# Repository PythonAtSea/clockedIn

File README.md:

# ClockedIn

> stupid name i know

insert readme stuffsies

## BOM
| Name | Link | Price |
|---|---|---|
| PCB + Case from JLC | N/A | $105.50 |
| M4 Heatset inserts | https://www.aliexpress.us/item/3256806611972099.html | $5.97 |
| M4 Screws | https://www.aliexpress.us/item/3256806025233809.html | $1.93 |
| 20 AWG wire | https://www.aliexpress.us/item/3256806379805687.html | $2.70 |
| M4 Standoff | https://www.aliexpress.us/item/3256805863280885.html | $2.72 |
| GPS Module | https://www.adafruit.com/product/746 | $29.95 |
| Coin Cell battery | https://www.adafruit.com/product/380 | $0.95 |
| GPS Adapter cable | https://www.adafruit.com/product/851 | $3.95 |
| GPS Antenna | https://www.adafruit.com/product/1858 | $5.95 |
| Adafruit shipping | N/A | $15.75 |
| 170V Boost converter | https://omnixie.com/products/nch8200hv-nixie-hv-power-module | $24.95 |
| TPIC6B595N | https://www.digikey.com/en/products/detail/texas-instruments/TPIC6B595N/277601 | $17.60 |
| 16-00019 | https://www.digikey.com/en/products/detail/tensility-international-corp/16-00019/10324408 | $6.71 |
| FMP100JR-52-22K | https://www.digikey.com/en/products/detail/yageo/FMP100JR-52-22K/2058593 | $1.66 |
| PJ-065B | https://www.digikey.com/en/products/detail/same-sky-formerly-cui-devices/PJ-065B/2627224 | $2.51 |
| DigiKey shipping | N/A | $6.99 |
| Nixie tubes | https://www.ebay.com/itm/286690956001 | $39.71 |
| Nixie tube socket pins | https://www.etsy.com/listing/856456136/gold-plated-nixievfd-tube-socket-pins | $14.50 |

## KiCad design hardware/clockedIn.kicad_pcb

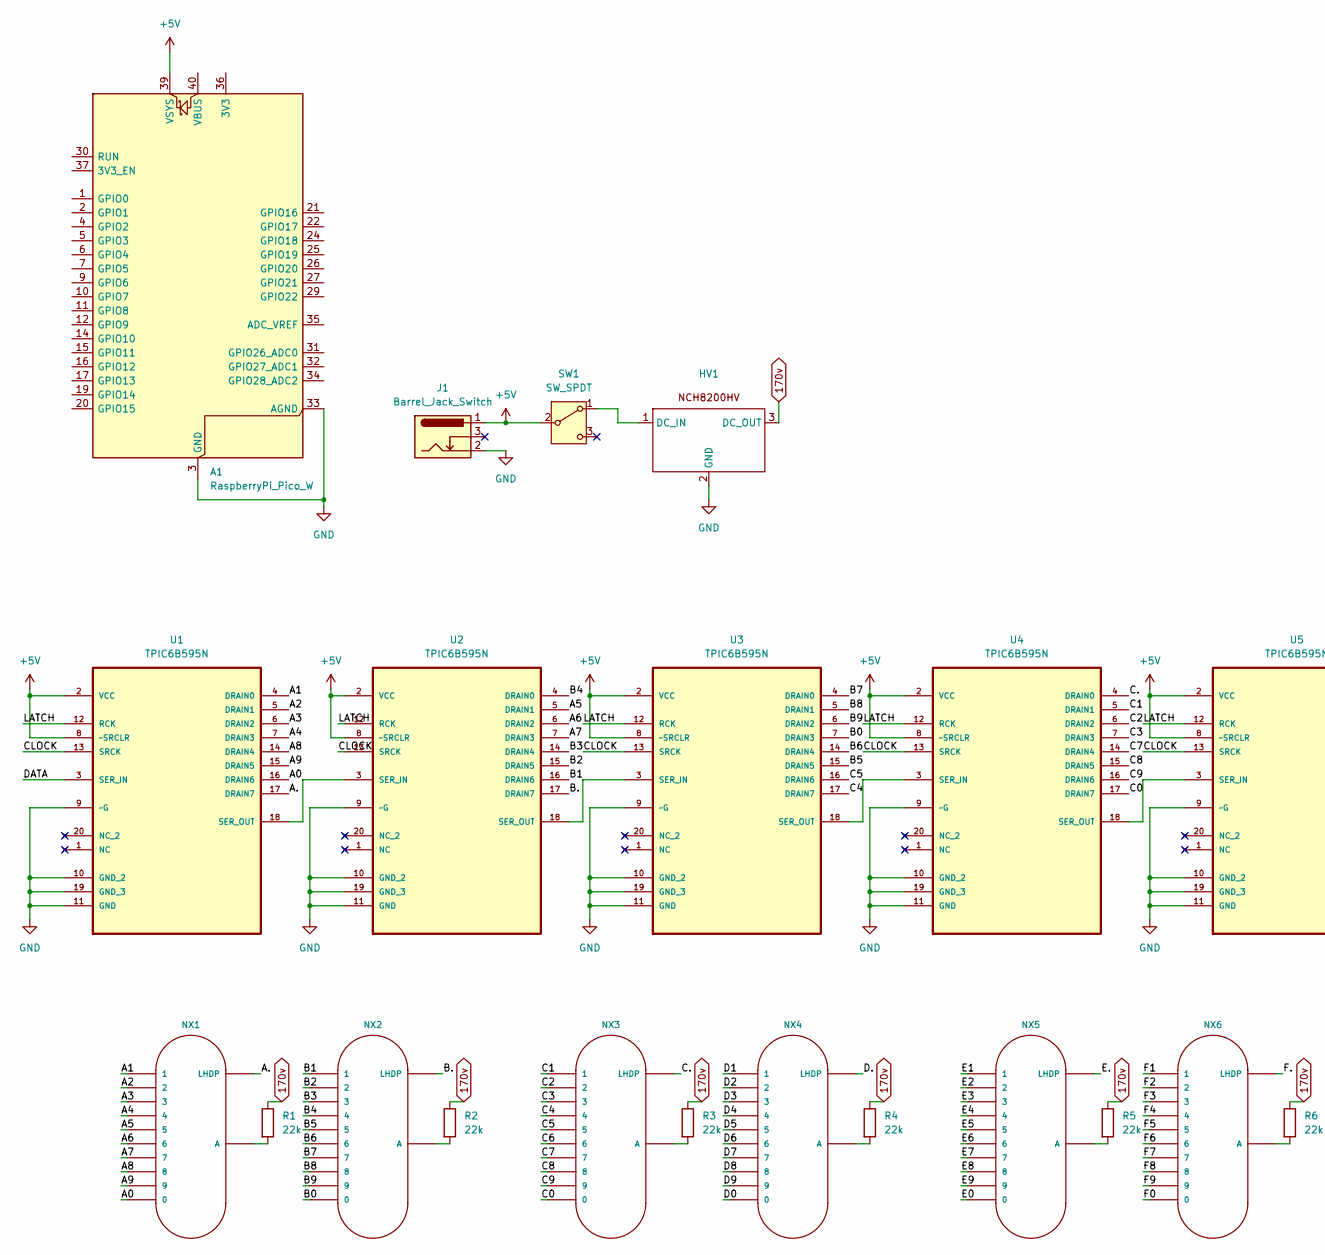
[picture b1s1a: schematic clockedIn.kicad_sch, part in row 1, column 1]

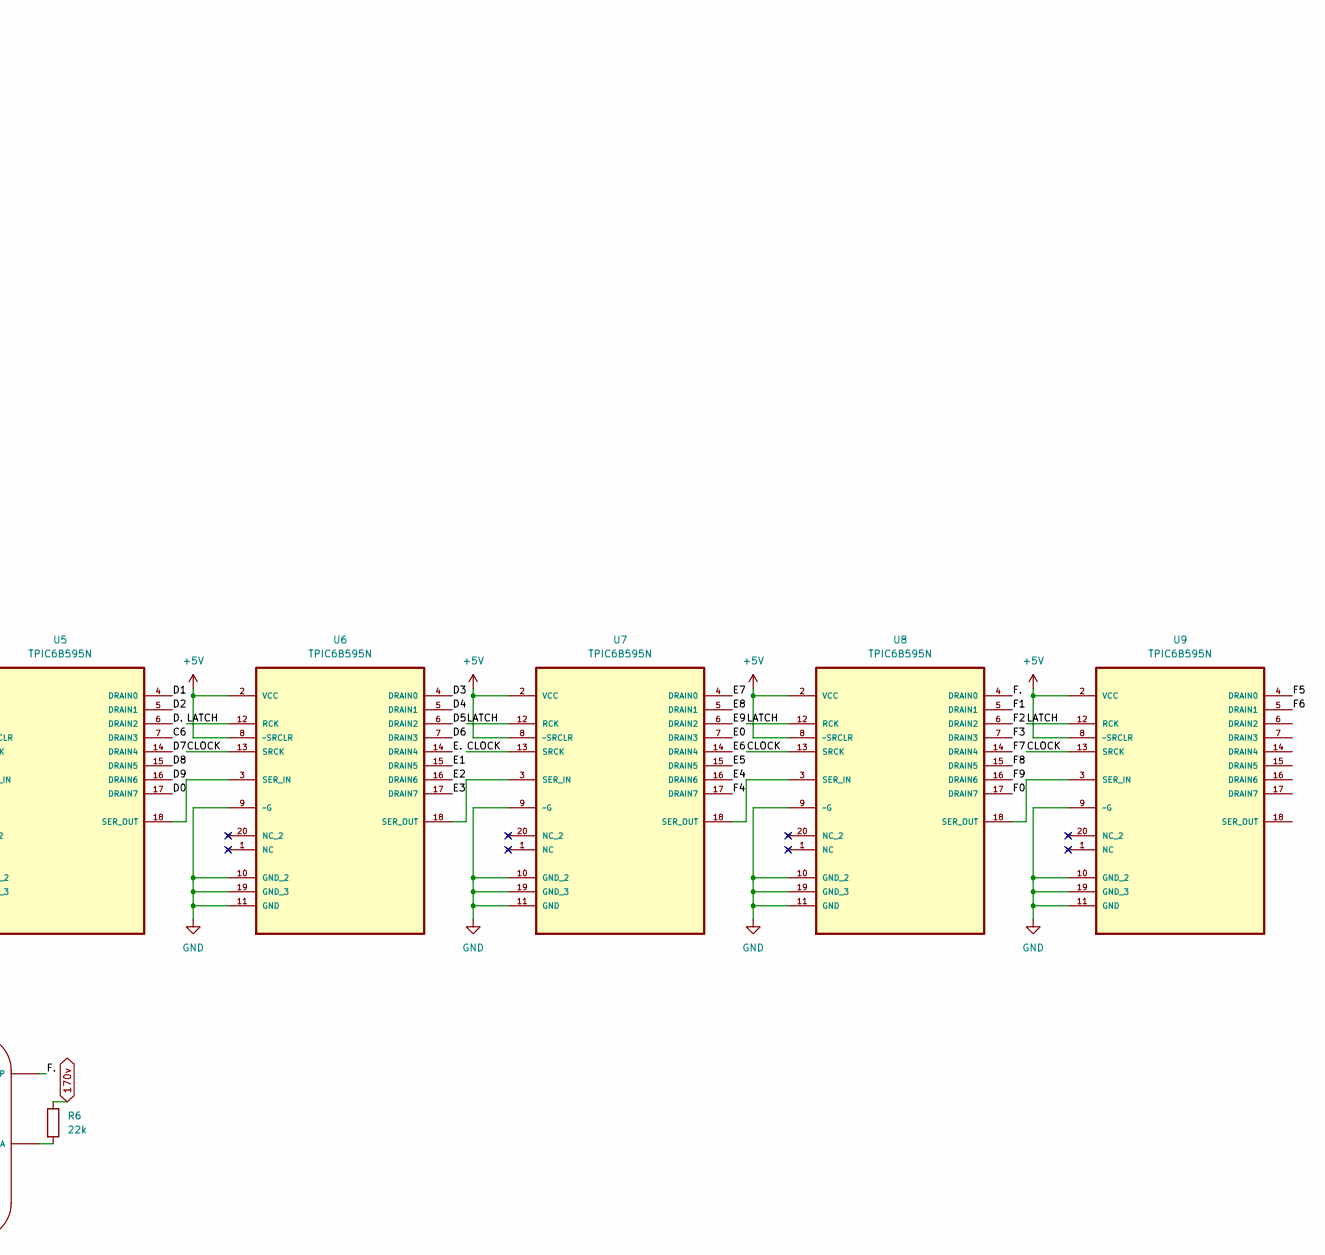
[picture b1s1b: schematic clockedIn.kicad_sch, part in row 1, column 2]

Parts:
A1: RaspberryPi_Pico_W; RaspberryPi_Pico_W_SMD_HandSolder
HV1: NCH8200HV
J1: Barrel_Jack_Switch
NX1, NX2, NX3, NX4, NX5, NX6: IN-12BORIGINAL; IN-12
R1, R2, R3, R4, R5, R6: 22k; R_Axial_DIN0207_L6.3mm_D2.5mm_P10.16mm_Horizontal
SW1: SW_SPDT; SW_500SSP3S1M6QEA
U1, U2, U3, U4, U5, U6, U7, U8, U9: TPIC6B595N; DIP254P762X508-20; MPN TPIC6B595N

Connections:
170v: HV1.3 (DC_OUT), R1.1, R2.1, R3.1, R4.1, R5.1, R6.1
+5V: A1.39 (VSYS), J1.1, SW1.2 (B), U1.2 (VCC), U1.8 (~SRCLR), U2.2 (VCC), U2.8 (~SRCLR), U3.2 (VCC), U3.8 (~SRCLR), U4.2 (VCC), U4.8 (~SRCLR), U5.2 (VCC), U5.8 (~SRCLR), U6.2 (VCC), U6.8 (~SRCLR), U7.2 (VCC), U7.8 (~SRCLR), U8.2 (VCC), U8.8 (~SRCLR), U9.2 (VCC), U9.8 (~SRCLR)
/A0: NX1.0, U1.16 (DRAIN6)
/A1: NX1.1, U1.4 (DRAIN0)
/A2: NX1.2, U1.5 (DRAIN1)
/A3: NX1.3, U1.6 (DRAIN2)
/A4: NX1.4, U1.7 (DRAIN3)
/A5: NX1.5, U2.5 (DRAIN1)
/A6: NX1.6, U2.6 (DRAIN2)
/A7: NX1.7, U2.7 (DRAIN3)
/A8: NX1.8, U1.14 (DRAIN4)
/A9: NX1.9, U1.15 (DRAIN5)
/A.: NX1.LHDP, U1.17 (DRAIN7)
/B0: NX2.0, U3.7 (DRAIN3)
/B1: NX2.1, U2.16 (DRAIN6)
/B2: NX2.2, U2.15 (DRAIN5)
/B3: NX2.3, U2.14 (DRAIN4)
/B4: NX2.4, U2.4 (DRAIN0)
/B5: NX2.5, U3.15 (DRAIN5)
/B6: NX2.6, U3.14 (DRAIN4)
/B7: NX2.7, U3.4 (DRAIN0)
/B8: NX2.8, U3.5 (DRAIN1)
/B9: NX2.9, U3.6 (DRAIN2)
/B.: NX2.LHDP, U2.17 (DRAIN7)
/C0: NX3.0, U4.17 (DRAIN7)
/C1: NX3.1, U4.5 (DRAIN1)
/C2: NX3.2, U4.6 (DRAIN2)
/C3: NX3.3, U4.7 (DRAIN3)
/C4: NX3.4, U3.17 (DRAIN7)
/C5: NX3.5, U3.16 (DRAIN6)
/C6: NX3.6, U5.7 (DRAIN3)
/C7: NX3.7, U4.14 (DRAIN4)
/C8: NX3.8, U4.15 (DRAIN5)
/C9: NX3.9, U4.16 (DRAIN6)
/C.: NX3.LHDP, U4.4 (DRAIN0)
/CLOCK: U1.13 (SRCK), U2.13 (SRCK), U3.13 (SRCK), U4.13 (SRCK), U5.13 (SRCK), U6.13 (SRCK), U7.13 (SRCK), U8.13 (SRCK), U9.13 (SRCK)
/D0: NX4.0, U5.17 (DRAIN7)
/D1: NX4.1, U5.4 (DRAIN0)
/D2: NX4.2, U5.5 (DRAIN1)
/D3: NX4.3, U6.4 (DRAIN0)
/D4: NX4.4, U6.5 (DRAIN1)
/D5: NX4.5, U6.6 (DRAIN2)
/D6: NX4.6, U6.7 (DRAIN3)
/D7: NX4.7, U5.14 (DRAIN4)
/D8: NX4.8, U5.15 (DRAIN5)
/D9: NX4.9, U5.16 (DRAIN6)
/D.: NX4.LHDP, U5.6 (DRAIN2)
/DATA: U1.3 (SER_IN)
/E0: NX5.0, U7.7 (DRAIN3)
/E1: NX5.1, U6.15 (DRAIN5)
/E2: NX5.2, U6.16 (DRAIN6)
/E3: NX5.3, U6.17 (DRAIN7)
/E4: NX5.4, U7.16 (DRAIN6)
/E5: NX5.5, U7.15 (DRAIN5)
/E6: NX5.6, U7.14 (DRAIN4)
/E7: NX5.7, U7.4 (DRAIN0)
/E8: NX5.8, U7.5 (DRAIN1)
/E9: NX5.9, U7.6 (DRAIN2)
/E.: NX5.LHDP, U6.14 (DRAIN4)
/F0: NX6.0, U8.17 (DRAIN7)
/F1: NX6.1, U8.5 (DRAIN1)
/F2: NX6.2, U8.6 (DRAIN2)
/F3: NX6.3, U8.7 (DRAIN3)
/F4: NX6.4, U7.17 (DRAIN7)
/F5: NX6.5, U9.4 (DRAIN0)
/F6: NX6.6, U9.5 (DRAIN1)
/F7: NX6.7, U8.14 (DRAIN4)
/F8: NX6.8, U8.15 (DRAIN5)
/F9: NX6.9, U8.16 (DRAIN6)
/F.: NX6.LHDP, U8.4 (DRAIN0)
/LATCH: U1.12 (RCK), U2.12 (RCK), U3.12 (RCK), U4.12 (RCK), U5.12 (RCK), U6.12 (RCK), U7.12 (RCK), U8.12 (RCK), U9.12 (RCK)
GND: A1.3 (GND), A1.8 (GND), A1.13 (GND), A1.18 (GND), A1.23 (GND), A1.28 (GND), A1.33 (AGND), A1.38 (GND), HV1.2 (GND), J1.2, U1.9 (~G), U1.10 (GND_2), U1.11 (GND), U1.19 (GND_3), U2.9 (~G), U2.10 (GND_2), U2.11 (GND), U2.19 (GND_3), U3.9 (~G), U3.10 (GND_2), U3.11 (GND), U3.19 (GND_3), U4.9 (~G), U4.10 (GND_2), U4.11 (GND), U4.19 (GND_3), U5.9 (~G), U5.10 (GND_2), U5.11 (GND), U5.19 (GND_3), U6.9 (~G), U6.10 (GND_2), U6.11 (GND), U6.19 (GND_3), U7.9 (~G), U7.10 (GND_2), U7.11 (GND), U7.19 (GND_3), U8.9 (~G), U8.10 (GND_2), U8.11 (GND), U8.19 (GND_3), U9.9 (~G), U9.10 (GND_2), U9.11 (GND), U9.19 (GND_3)
unnamed: HV1.1 (DC_IN), SW1.1 (A)
unnamed: NX1.A, R1.2
unnamed: NX2.A, R2.2
unnamed: NX3.A, R3.2
unnamed: NX4.A, R4.2
unnamed: NX5.A, R5.2
unnamed: NX6.A, R6.2
unnamed: U1.18 (SER_OUT), U2.3 (SER_IN)
unnamed: U2.18 (SER_OUT), U3.3 (SER_IN)
unnamed: U3.18 (SER_OUT), U4.3 (SER_IN)
unnamed: U4.18 (SER_OUT), U5.3 (SER_IN)
unnamed: U5.18 (SER_OUT), U6.3 (SER_IN)
unnamed: U6.18 (SER_OUT), U7.3 (SER_IN)
unnamed: U7.18 (SER_OUT), U8.3 (SER_IN)
unnamed: U8.18 (SER_OUT), U9.3 (SER_IN)

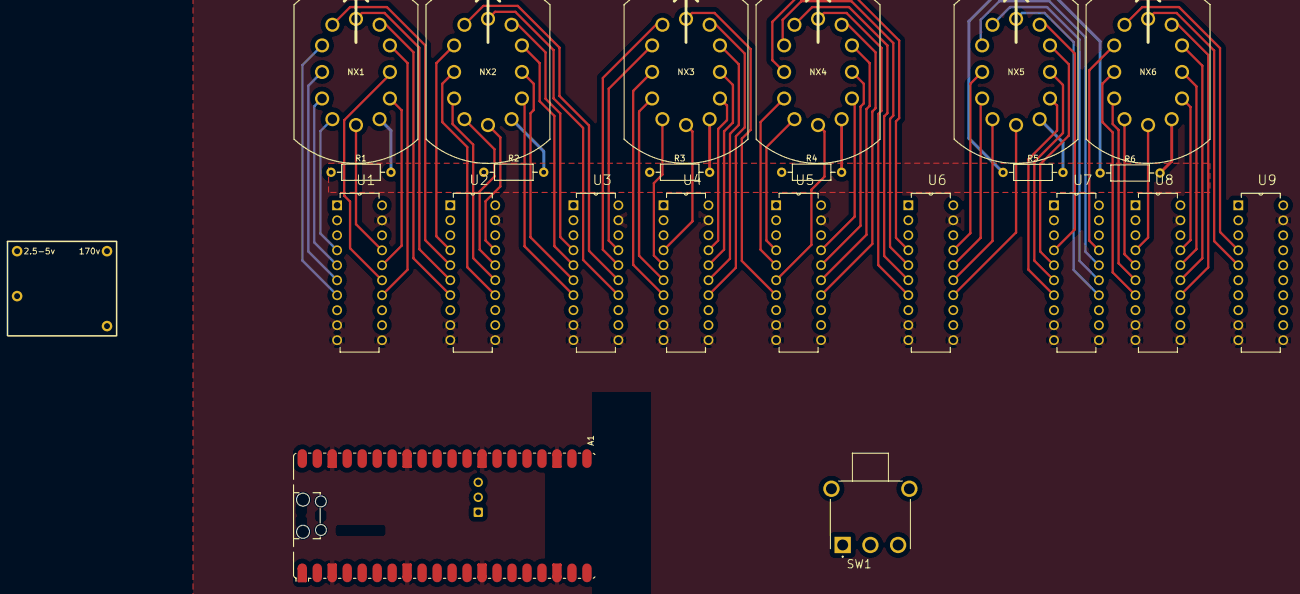
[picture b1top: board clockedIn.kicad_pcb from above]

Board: 2 copper layers, 24 parts (0 on the bottom side), 86 nets.

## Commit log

2025-06-16 stuff
2025-06-18 journalllllll
2025-06-19 maybe i should commit the hardware files :sob:
2025-06-20 hardware bump
2025-06-20 footprints
2025-06-21 bwahahahaha idk what im saying atp
2025-06-21 nixienixienixienixienixienixienixie
2025-06-21 hardware files update
2025-06-22 hardwareisveryhard
2025-07-06 expensive
